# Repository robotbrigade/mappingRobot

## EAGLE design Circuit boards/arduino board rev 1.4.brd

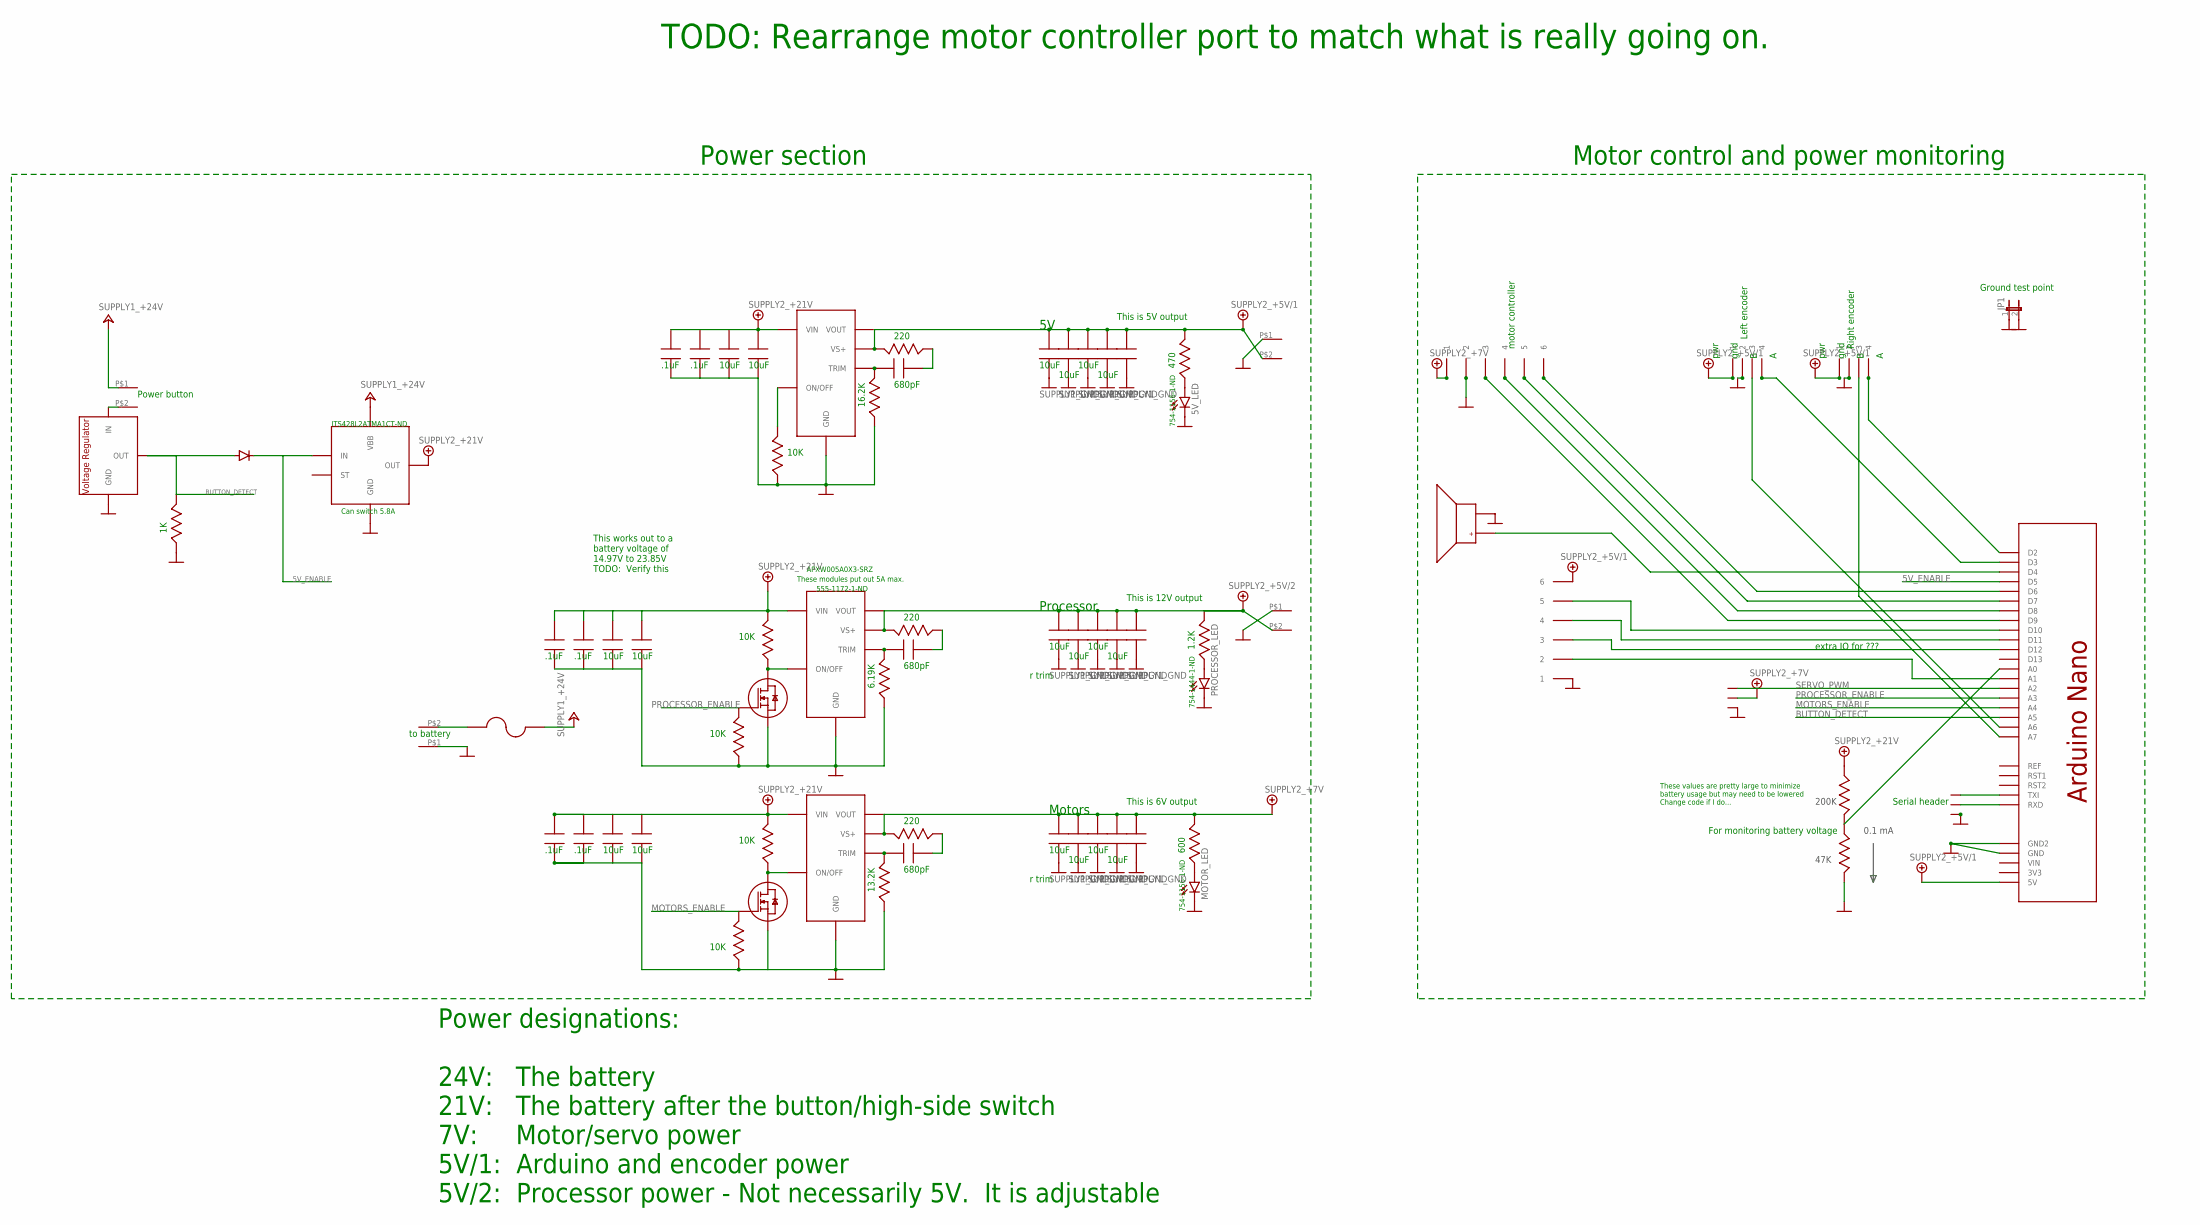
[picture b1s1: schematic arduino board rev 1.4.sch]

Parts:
5V_C_680PF: JACK_CAPACITOR0805; JACK_0805
5V_IN_CAP_1, 5V_IN_CAP_2, 5V_IN_CAP_3, 5V_IN_CAP_4, 5V_OUT_CAP_1, 5V_OUT_CAP_2, 5V_OUT_CAP_3, 5V_OUT_CAP_4, 5V_OUT_CAP_5: JACK_CAPACITOR; JACK_1210
5V_LED: LED_LEDSML1206; LED_SML1206
5V_LED_R1, 5V_REGULATOR_PULLDOWN, 5V_R_220: JACK_RESISTOR0805; JACK_0805
BATTERY_VOLTAGE_DIVIDER_HIGH: JACK_RESISTOR0805; JACK_0805
BATTERY_VOLTAGE_DIVIDER_LOW: JACK_RESISTOR0805; JACK_0805
BEEPER: JACK_BEEPER; JACK_BEEPER_433-1033-ND
DC2DC_PROCESSOR_: JACK_DC_TO_DC_VARIABLE_555-1172-1-ND; JACK_DC2DC_555-1172-1-ND
HIGH-SIDE_BLOCKING_DIODE: JACK_DIODESOD-23/SC-76; JACK_SOD-323/SC-76
HIGH-SIDE_SWITCH: JACK_HIGH-SIDE_SWITCH_INFINEON_ITS428L2; JACK_INFINEON_TO-252-5-11
HIGH-SIDE_SWITCH_BUTTON_DIVIDER_LOW: JACK_RESISTOR0805; JACK_0805
JP1: JUMPER_JP1E; JUMPER_JP1
MOTOR.1UF: JACK_CAPACITOR; JACK_1210
MOTOR_C_680PF: JACK_CAPACITOR0805; JACK_0805
MOTOR_ENABLE_MOSFET: JACK_MOSFET_N_CHANNELBSS138LCT-ND; JACK_SOT23
MOTOR_IN10UF, MOTOR_IN.1UF, MOTOR_IN.1UF1, MOTOR_IN.1UF4: JACK_CAPACITOR; JACK_1210
MOTOR_LED: LED_LEDSML1206; LED_SML1206
MOTOR_LED_R: JACK_RESISTOR0805; JACK_0805
MOTOR_MOSFET_PULLDOWN: JACK_RESISTOR0805; JACK_0805
MOTOR_PULLUP: JACK_RESISTOR0805; JACK_0805
MOTOR_R_220: JACK_RESISTOR0805; JACK_0805
MOTOR_TRIM: JACK_RESISTOR0805; JACK_0805
MOTOTR10UF, MOTOTR10UF1, MOTOTR10UF2, MOTOTR10UF3: JACK_CAPACITOR; JACK_1210
PROC10UF, PROC10UF1, PROC10UF2, PROC10UF3, PROC.1UF: JACK_CAPACITOR; JACK_1210
PROCESSOR_C_680PF: JACK_CAPACITOR0805; JACK_0805
PROCESSOR_ENABLE_MOSFET: JACK_MOSFET_N_CHANNELBSS138LCT-ND; JACK_SOT23
PROCESSOR_LED: LED_LEDSML1206; LED_SML1206
PROCESSOR_LED_R: JACK_RESISTOR0805; JACK_0805
PROCESSOR_MOSFET_PULLDOWN: JACK_RESISTOR0805; JACK_0805
PROCESSOR_PULLUP: JACK_RESISTOR0805; JACK_0805
PROCESSOR_R_220: JACK_RESISTOR0805; JACK_0805
PROC_IN10UF: JACK_CAPACITOR; JACK_1210
PROC_IN_.1UF, PROC_IN_.1UF1, PROC_IN_.1UF2: JACK_CAPACITOR; JACK_1210
RTRIM_5V: JACK_RESISTOR0805; JACK_0805
RTRIM_PROCESSOR: JACK_RESISTOR0805; JACK_0805
SERVO_HEADER: JACK_CONNECTOR_3_PIN; JACK_THREE_.1"_HOLES
U$1, U$2, U$5, U$6: JACK_SCREW_TERMINAL_2_CONDUCTORAMP-282837-2; JACK_AMP-282837-2
U$3, U$9: JACK_CONNECTOR_6_PINJST_MAYBE; JACK_JST_6_PIN_.1"
U$4, U$17: JACK_DC_TO_DC_VARIABLE_555-1172-1-ND; JACK_DC2DC_555-1172-1-ND
U$7: VOLTAGE_REGULATOR; JACK_SOT23
U$10, U$12: JACK_CONNECTOR_4_PIN; JACK_JST_4_PIN_.1"
U$11: JACK_FUSE_HOLDER_F065-ND; JACK_FUSE_HOLDER_F064-ND
U$13: JACK_CONNECTOR_3_PINMAYBE_JST; JACK_JST_3_PIN_.1"
U$14: JACK_ARDUINO_NANO

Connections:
5V_ENABLE: HIGH-SIDE_BLOCKING_DIODE.C, HIGH-SIDE_SWITCH.2 (IN), U$14.P$8 (D5)
+5V/1: 5V_LED_R1.P$3, 5V_OUT_CAP_1.2, 5V_OUT_CAP_2.2, 5V_OUT_CAP_3.2, 5V_OUT_CAP_4.2, 5V_OUT_CAP_5.2, 5V_R_220.P$3, U$2.P$2, U$3.6, U$4.VOUT, U$4.VS+, U$10.1, U$12.1, U$14.P$19 (5V)
+5V/2: DC2DC_PROCESSOR_.VOUT, DC2DC_PROCESSOR_.VS+, PROC10UF.2, PROC10UF1.2, PROC10UF2.2, PROC10UF3.2, PROC.1UF.2, PROCESSOR_LED_R.P$3, PROCESSOR_R_220.P$3, U$5.P$2
+7V: MOTOR.1UF.2, MOTOR_LED_R.P$3, MOTOR_R_220.P$3, MOTOTR10UF.2, MOTOTR10UF1.2, MOTOTR10UF2.2, MOTOTR10UF3.2, SERVO_HEADER.2, U$9.1, U$17.VOUT, U$17.VS+
+21V: 5V_IN_CAP_1.2, 5V_IN_CAP_2.2, 5V_IN_CAP_3.2, 5V_IN_CAP_4.2, BATTERY_VOLTAGE_DIVIDER_HIGH.P$2, DC2DC_PROCESSOR_.VIN, HIGH-SIDE_SWITCH.5 (OUT), MOTOR_IN10UF.2, MOTOR_IN.1UF.2, MOTOR_IN.1UF1.2, MOTOR_IN.1UF4.2, MOTOR_PULLUP.P$3, PROCESSOR_PULLUP.P$3, PROC_IN10UF.2, PROC_IN_.1UF.2, PROC_IN_.1UF1.2, PROC_IN_.1UF2.2, U$4.VIN, U$17.VIN
+24V: HIGH-SIDE_SWITCH.TAB (VBB), U$1.P$1, U$11.P$1
BUTTON_DETECT: HIGH-SIDE_BLOCKING_DIODE.A, HIGH-SIDE_SWITCH_BUTTON_DIVIDER_LOW.P$3, U$7.1 (OUT), U$14.P$22 (A5)
GND: 5V_IN_CAP_1.1, 5V_IN_CAP_2.1, 5V_IN_CAP_3.1, 5V_IN_CAP_4.1, 5V_LED.C, 5V_OUT_CAP_1.1, 5V_OUT_CAP_2.1, 5V_OUT_CAP_3.1, 5V_OUT_CAP_4.1, 5V_OUT_CAP_5.1, 5V_REGULATOR_PULLDOWN.P$2, BATTERY_VOLTAGE_DIVIDER_LOW.P$3, BEEPER.-, DC2DC_PROCESSOR_.GND, HIGH-SIDE_SWITCH.1 (GND), HIGH-SIDE_SWITCH_BUTTON_DIVIDER_LOW.P$2, JP1.1, JP1.2, MOTOR.1UF.1, MOTOR_ENABLE_MOSFET.2 (S), MOTOR_IN10UF.1, MOTOR_IN.1UF.1, MOTOR_IN.1UF1.1, MOTOR_IN.1UF4.1, MOTOR_LED.C, MOTOR_MOSFET_PULLDOWN.P$2, MOTOR_TRIM.P$2, MOTOTR10UF.1, MOTOTR10UF1.1, MOTOTR10UF2.1, MOTOTR10UF3.1, PROC10UF.1, PROC10UF1.1, PROC10UF2.1, PROC10UF3.1, PROC.1UF.1, PROCESSOR_ENABLE_MOSFET.2 (S), PROCESSOR_LED.C, PROCESSOR_MOSFET_PULLDOWN.P$2, PROC_IN10UF.1, PROC_IN_.1UF.1, PROC_IN_.1UF1.1, PROC_IN_.1UF2.1, RTRIM_5V.P$2, RTRIM_PROCESSOR.P$2, SERVO_HEADER.1, U$2.P$1, U$3.1, U$4.GND, U$5.P$1, U$6.P$1, U$7.3 (GND), U$9.2, U$10.2, U$12.2, U$13.1, U$14.P$12 (GND), U$14.P$17 (GND2), U$17.GND
IN: U$1.P$2, U$7.2 (IN)
MOTORS_ENABLE: MOTOR_ENABLE_MOSFET.1 (G), MOTOR_MOSFET_PULLDOWN.P$3, U$14.P$23 (A4)
unnamed: PROCESSOR_LED.A, PROCESSOR_LED_R.P$2
unnamed: MOTOR_LED.A, MOTOR_LED_R.P$2
unnamed: DC2DC_PROCESSOR_.ON/OFF, PROCESSOR_ENABLE_MOSFET.3 (D), PROCESSOR_PULLUP.P$2
unnamed: U$12.3, U$14.P$20 (A7)
unnamed: U$3.5, U$14.P$3 (D10)
unnamed: MOTOR_ENABLE_MOSFET.3 (D), MOTOR_PULLUP.P$2, U$17.ON/OFF
unnamed: U$9.6, U$14.P$7 (D6)
unnamed: U$12.4, U$14.P$11 (D2)
unnamed: U$6.P$2, U$11.P$2
unnamed: U$13.3, U$14.P$15 (TXI)
unnamed: U$13.2, U$14.P$14 (RXD)
unnamed: U$10.4, U$14.P$10 (D3)
unnamed: U$10.3, U$14.P$21 (A6)
unnamed: BEEPER.+, U$14.P$9 (D4)
unnamed: U$9.5, U$14.P$6 (D7)
unnamed: U$9.4, U$14.P$5 (D8)
unnamed: U$9.3, U$14.P$4 (D9)
unnamed: 5V_C_680PF.P$3 (2), RTRIM_5V.P$3, U$4.TRIM
unnamed: U$3.2, U$14.P$26 (A1)
unnamed: U$3.4, U$14.P$2 (D11)
unnamed: 5V_LED.A, 5V_LED_R1.P$2
unnamed: BATTERY_VOLTAGE_DIVIDER_HIGH.P$3, BATTERY_VOLTAGE_DIVIDER_LOW.P$2, U$14.P$27 (A0)
unnamed: U$3.3, U$14.P$1 (D12)
unnamed: 5V_REGULATOR_PULLDOWN.P$3, U$4.ON/OFF
unnamed: 5V_C_680PF.P$2 (1), 5V_R_220.P$2
unnamed: DC2DC_PROCESSOR_.TRIM, PROCESSOR_C_680PF.P$3 (2), RTRIM_PROCESSOR.P$3
unnamed: MOTOR_C_680PF.P$3 (2), MOTOR_TRIM.P$3, U$17.TRIM
unnamed: PROCESSOR_C_680PF.P$2 (1), PROCESSOR_R_220.P$2
unnamed: MOTOR_C_680PF.P$2 (1), MOTOR_R_220.P$2
PROCESSOR_ENABLE: PROCESSOR_ENABLE_MOSFET.1 (G), PROCESSOR_MOSFET_PULLDOWN.P$3, U$14.P$24 (A3)
SERVO_PWM: SERVO_HEADER.3, U$14.P$25 (A2)

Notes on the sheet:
to battery
Left encoder
Right encoder
motor controller
pwr
gnd
For monitoring battery voltage
extra IO for ???
r trim
Processor
Motors
Power section
Motor control and power monitoring
754-1156-1-ND
754-1444-1-ND
Ground test point
200K
47K
0.1 mA
Serial header
Power designations: 24V: The battery 21V: The battery after the button/high-side switch 7V: Motor/servo power 5V/1: Arduino and encoder power 5V/2: Processor power - Not necessarily 5V. It is adjustable
This works out to a battery voltage of 14.97V to 23.85V TODO: Verify this
These values are pretty large to minimize battery usage but may need to be lowered Change code if I do...
These modules put out 5A max.
555-1172-1-ND
APXW005A0X3-SRZ
ITS428L2ATMA1CT-ND
Can switch 5.8A
Power button
10K
This is 12V output
This is 6V output
This is 5V output
6.19K
13.2K
16.2K
220
680pF
10uF
.1uF

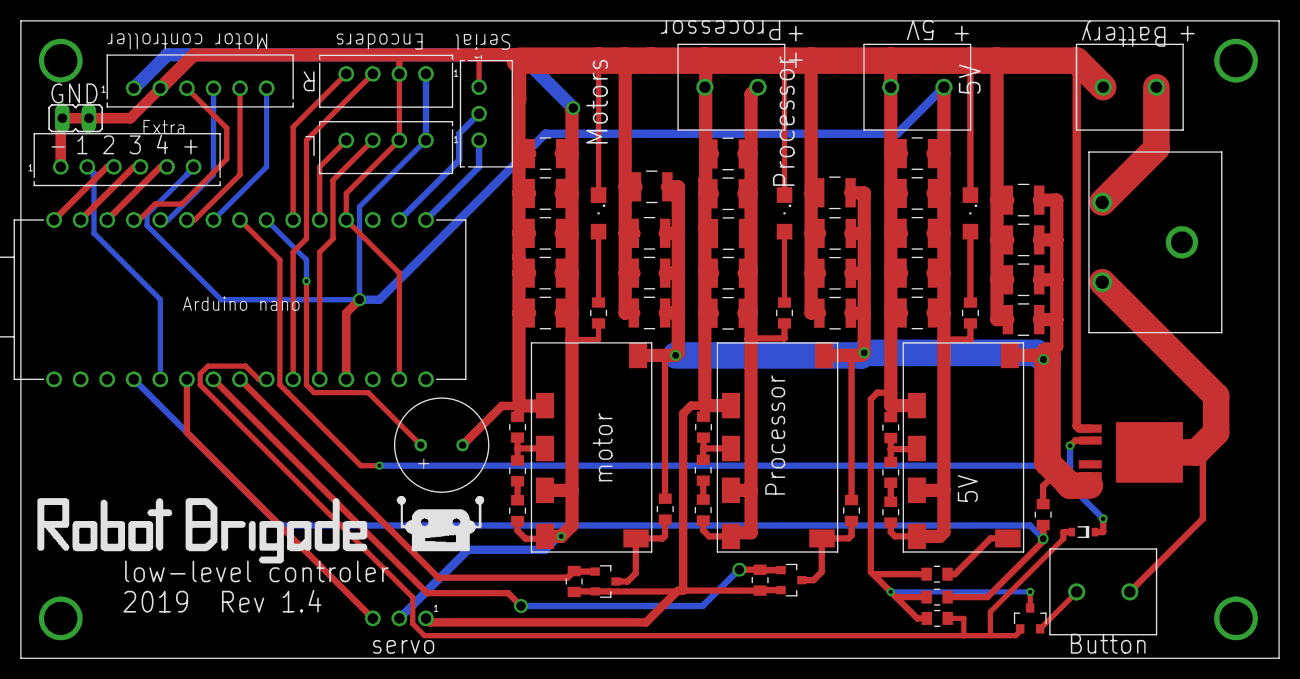
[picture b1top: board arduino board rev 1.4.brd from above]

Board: 2 copper layers, 120.3 x 61.0 mm, 73 parts (0 on the bottom side), 41 nets.

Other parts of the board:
U$8: ROBOT_BRIGADE_LOGO_AND_TEXT_.2"

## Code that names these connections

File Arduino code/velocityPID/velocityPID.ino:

/*   Firmware for Arduino board V4

     Written by Jack Buffington 2019 with the exception of the Morse Code beep functions, which are lightly modified from
     what can be found on the Arduino website.

     This board controls the motors and power for the mapping robot.  It is tasked with the following:
 *   * Drive according to commands given by the main processor
 *   * Control the power to the main processor, motors, and itself.
 *   * Monitor the battery voltage
 *   * Track position via encoders
 *   * Output beep or tone codes via a speaker
 *   * Determines if a wheel is stuck
 *   * Monitors bump sensors

     Control of this board will be done via serial data <TODO:  Verify that this is true.  It could be through USB serial.>

     This program will address serial commands through the main loop and will do the real-time tasks such as PID and reading
     the encoders from within interrupts.

     This program maintains a status byte which can be sent to the host processor.  The status byte is as follows:
     
    Status byte: <76543210>
    bit 7: in motion
    bit 6: left wheel stuck
    bit 5: right wheel stuck
    bit 4: bump sensor pressed
    bit 3: extra 4 is high
    bit 2: extra 3 is high
    bit 1: extra 2 is high
    bit 0: last motion completed successfully


    To program my Arduino clone, I need to select the processor as ATMEGA328P (Old Bootloader) otherwise I get a bunch of this:
    
    avrdude: stk500_recv(): programmer is not responding
    avrdude: stk500_getsync() attempt 1 of 10: not in sync: resp=0x00
    avrdude: stk500_recv(): programmer is not responding
    avrdude: stk500_getsync() attempt 2 of 10: not in sync: resp=0x00

     
     

*/

#define VOLTAGE_DETECT        A0
#define SERVO_PWM             A2
#define PROCESSOR_ENABLE      A3
#define MOTORS_ENABLE         A4
#define BUTTON                A5

#define MAIN_POWER_ENABLE     5
#define BEEPER                4

#define RIGHT_ENCODER_A       3
#define RIGHT_ENCODER_B       6
#define LEFT_ENCODER_A        2
#define LEFT_ENCODER_B        11


#define LEFT_MOTOR_PWM        10    // Pins 9 and 10 are capable of analog write.  The control scheme will need to take into account
#define LEFT_MOTOR_DIRECTION  7   // the direction and sometimes invert the PWM to match the actual desired speed.  The two pins 
#define RIGHT_MOTOR_DIRECTION 8    // for each motor correspond to the two outputs for the motor or in other words, the L298 is actually
#define RIGHT_MOTOR_PWM       9    // A quad half bridge device with the enables done in pairs.  


#define EXTRA_IO_4            A7   // A7 is analog input only!
#define EXTRA_IO_3            A6   // A6 is analog input only!
#define EXTRA_IO_2            12
#define EXTRA_IO_1            A1
#define LED                   13

// 14.97V is where my drill considers the battery to be dead
// After sitting for a while, a freshly charged battery is at 20.2V
#define BATTERY_FULL          20200
#define BATTERY_DEAD          15000

//#define SERIAL_BUFFER_SIZE    8
//// queue depth is how many messages can be waiting for the main program at any given time.
//#define QUEUE_DEPTH           3




//
// PID control values (yes, I did play with the values but this ended up working good enough...)
// You may want to play with them more if you need to make more rapid starts and stops to avoid oscillation.  
#define P_TERM                1 // 2       
#define D_TERM                1 // 3   






// for motor control
//unsigned int interruptsLeft = 0; // Used for determining how far to drive
int desiredLeftVelocity = 0;   // Used by the PID interrupt routine.  Don't write to these directly.  Let setupMotion() write to them.
int desiredRightVelocity = 0;


// For communicating with the PID interrupt
int rampingUpTimeslotsGlobal;
int rampingDownTimeslotsGlobal;
int constantTimeslotsGlobal;
int leftMaxVelocityGlobal;
int rightMaxVelocityGlobal;
int leftAccelerationGlobal;
int rightAccelerationGlobal;
volatile bool inMotion = false; // Volatile so that the compiler doesn't optimize away loops waiting for it to change.
 

// For keeping track of position
long leftEncoder;   // Actual position of the encoder
long rightEncoder; 
int  leftEncoderVelocity; // This is reset every interrupt and is used for PID calculations
int  rightEncoderVelocity;


void setup()
{
  // Enable power to the whole board without requiring that the user hold the button.  
  digitalWrite(MAIN_POWER_ENABLE, HIGH);

  // Wait a moment for power to stabilize then check the main battery voltage
  delay(100);

  // Set the pins to be inputs or outputs
  pinMode(VOLTAGE_DETECT, INPUT);
  pinMode(SERVO_PWM, OUTPUT);
  pinMode(PROCESSOR_ENABLE, OUTPUT);
  pinMode(MOTORS_ENABLE, OUTPUT);
  pinMode(BUTTON, INPUT);
  pinMode(MAIN_POWER_ENABLE, OUTPUT);
  pinMode(BEEPER, OUTPUT);
  pinMode(RIGHT_ENCODER_A, INPUT);
  pinMode(RIGHT_ENCODER_B, INPUT);
  pinMode(LEFT_ENCODER_A, INPUT);
  pinMode(LEFT_ENCODER_B, INPUT);
  pinMode(LEFT_MOTOR_PWM, OUTPUT);
  pinMode(LEFT_MOTOR_DIRECTION, OUTPUT);
  pinMode(RIGHT_MOTOR_PWM, OUTPUT);
  pinMode(RIGHT_MOTOR_DIRECTION, OUTPUT);
  pinMode(EXTRA_IO_4, OUTPUT);
  pinMode(EXTRA_IO_3, OUTPUT);
  pinMode(EXTRA_IO_2, OUTPUT);
  pinMode(EXTRA_IO_1, OUTPUT);
  pinMode(LED, OUTPUT);

  // Set up the USB serial port
  Serial.begin(2000000);

  beep(50,16000);
  beep(50,8000);
  beep(50,4000);
  beep(50,2000);
  beep(50,1000);
  beep(50,500);
  beep(50,250);
  beep(50,125);
  beep(50,62);

  setupMotorStuff();
} // end of setup()







void loop()
{  

  // Control the motors with ramping
  setupMotion(100, 300, 80, 8000);
  while(inMotion == true)
    { // Just hang out while the movement happens
    }
  Serial.println("A");


  
  setupMotion(-20, -300, 500, 3000);
  while(inMotion == true)
    { // Just hang out while the movement happens
    }
  Serial.println("B");
}










byte readBattery()
{ // outputs a value in the range of 0 to 100 which represents the roughly remaining capacity of the battery in percentage.ch tex
  

  /*
   *  Due to the voltage divider that I am using:  200K and 47K, this multiplies the voltage by .1903
   *  With 1024 counts for 5V, to get the voltage read, I need to multiply the counts by 5 and divide by 1024.
   *  To get the actual voltage of the battery, I would want to multiply that by 1/.1903.  To get this voltage, 
   *  it is roughly equivalent to multiplying by (1681/65536).  Of course, since we are dealing with only whole 
   *  numbers, this doesn't leave much resolution so this program is working in voltage * 1000.  This makes the 
   *  calculation be <analog reading> * (1681702/65536).  An unsigned long can handle the values in the range 
   *   0-4,294,967,295.  1681702 * 1024 (the max reading) is 1,722,062,848.  This will fit within an unsigned long!
   */
  unsigned long batteryVoltage;
  batteryVoltage = analogRead(VOLTAGE_DETECT); // gives me a value in the range of 0 to 1024.
  Serial.print("ADC reading: ");
  Serial.println(batteryVoltage);

  
  batteryVoltage *= 1681702;
  batteryVoltage >>= 16; // Make sure that the calculation is fast rather than doing a real division.
  Serial.print("voltage: ");
  Serial.println(batteryVoltage);
  
  

  // Calculate the rough remaining battery capacity based on a linear relationship to the voltage
  batteryVoltage -= BATTERY_DEAD;

  word batteryRange = BATTERY_FULL - BATTERY_DEAD;
  // Since I am working in integer math, I can't just divide batteryVoltage by the battery range since I
  // would get zero every time so I'm going to multiply the battery voltage by 100 first to give me a result in the range of
  // 0 to ~100.
  batteryVoltage *= 100;

  batteryVoltage /= batteryRange;

  if (batteryVoltage > 100) // It could be higher because I set the full voltage a little lower than what it really
    batteryVoltage = 100;   // is when it is full.

  return batteryVoltage;
}

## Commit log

2019-08-28 Added parts lists
2019-08-28 Added cad files and DXF files used for laser cutting
2019-09-03 Updated board test code and fixed circuit board's power-up issue
2019-09-04 Updated the boardtest file
2019-09-08 PID nearly tuned for position mode
2019-09-09 Velocity PID is tuned pretty well
2019-09-10 velocity PID is working now with no ramping
2019-09-12 Motor control is fully working now
